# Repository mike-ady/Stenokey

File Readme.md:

# Stenokey

Stenographic keyboard

Stenokey is an open source do it yourself stenographic keyboard project.  It is aimed 
at makers with some electronics experience (soldering) and who own a 3D printer 
or who have a friend with a 3D printer.

Stenokey connects to any desktop or laptop PC that has a USB port.  It is meant 
to work with the Open Steno Project's Plover software, which runs on Linux, Mac and 
Windows.

This project consists of four main parts:

- The OpenSCAD source code for all of the 3D printed plastic parts is in the main 
directory.  Printer ready .STL files for the key tops are in the Key\_Print\_Files 
directory.  The .STL files for the case are in the Case\_Print\_Files directory.  

- The bill of materials (BOM) for populating the circuit board is in the main 
directory.  The PCB design files are in the PCB directory.

- The Arduino based firmware is in the Firmware directory.

- Documentation for the project, including build instructions, programming and testing 
instructions and a user manual are all in the Documentation Directory.

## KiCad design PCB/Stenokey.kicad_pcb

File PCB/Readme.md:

# Stenokey PCB Readme

Copyright © 2017, Mike Ady  
This file is part of the open source Stenokey project.  
This file is licensed under the Creative Commons Attribution-ShareAlike license.

## Directory Listing

- Gerbers -- This directory holds the files that are required to have circuit boards made.

- Stenokey.pretty -- This directory is the footprint library for the Stenokey project.

- Stenokey.kicad_pcb -- This is the circuit board layout file.

- Stenokey.kicad_wks -- This is the title block and frame layout file.

- Stenokey.lib -- This is the schematic library for the Stenokey project.

- Stenokey.pro -- This is the KiCAD project file.

- StenoKey.sch -- This is the schematic file.

- StenoKeyLogo.kicad_wks -- This is the Stenokey logo in KiCAD format.

The remaining files and directories were program generated.

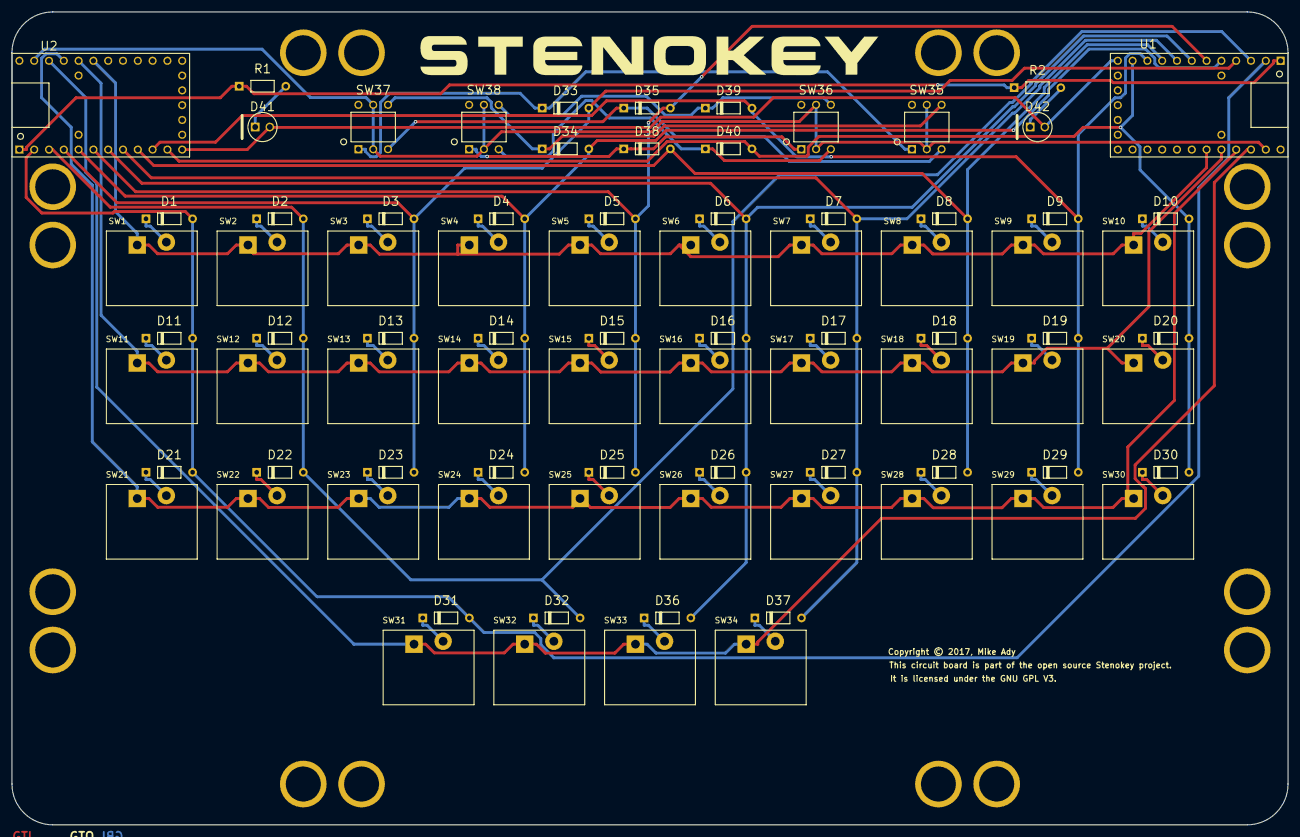
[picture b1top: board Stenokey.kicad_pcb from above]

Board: 2 copper layers, 219.0 x 139.5 mm, 102 parts (0 on the bottom side), 59 nets.

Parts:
D1, D2, D3, D4, D5, D6, D7, D8, D9, D10, D11, D12, D13, D14, D15, D16, D17, D18, D19, D20, D21, D22, D23, D24, D25, D26, D27, D28, D29, D30, D31, D32, D33, D34, D35, D36, D37, D38, D39, D40: DIODE; D4x2
D41, D42: LED; LED5X2.5
R1, R2: R; R4x2
SW1: KEY_R1C1; SW_Matias_Quiet
SW2: KEY_R1C2; SW_Matias_Quiet
SW3: KEY_R1C3; SW_Matias_Quiet
SW4: KEY_R1C4; SW_Matias_Quiet
SW5: KEY_R1C5; SW_Matias_Quiet
SW6: KEY_R1C6; SW_Matias_Quiet
SW7: KEY_R1C7; SW_Matias_Quiet
SW8: KEY_R1C8; SW_Matias_Quiet
SW9: KEY_R1C9; SW_Matias_Quiet
SW10: KEY_R1C10; SW_Matias_Quiet
SW11: KEY_R2C1; SW_Matias_Quiet
SW12: KEY_R2C2; SW_Matias_Quiet
SW13: KEY_R2C3; SW_Matias_Quiet
SW14: KEY_R2C4; SW_Matias_Quiet
SW15: KEY_R2C5; SW_Matias_Quiet
SW16: KEY_R2C6; SW_Matias_Quiet
SW17: KEY_R2C7; SW_Matias_Quiet
SW18: KEY_R2C8; SW_Matias_Quiet
SW19: KEY_R2C9; SW_Matias_Quiet
SW20: KEY_R2C10; SW_Matias_Quiet
SW21: KEY_R3C1; SW_Matias_Quiet
SW22: KEY_R3C2; SW_Matias_Quiet
SW23: KEY_R3C3; SW_Matias_Quiet
SW24: KEY_R3C4; SW_Matias_Quiet
SW25: KEY_R3C5; SW_Matias_Quiet
SW26: KEY_R3C6; SW_Matias_Quiet
SW27: KEY_R3C7; SW_Matias_Quiet
SW28: KEY_R3C8; SW_Matias_Quiet
SW29: KEY_R3C9; SW_Matias_Quiet
SW30: KEY_R3C10; SW_Matias_Quiet
SW31: KEY_R4C1; SW_Matias_Quiet
SW32: KEY_R4C2; SW_Matias_Quiet
SW33: KEY_R4C6; SW_Matias_Quiet
SW34: KEY_R4C7; SW_Matias_Quiet
SW35, SW36, SW37, SW38: SW_ENCODED; DIP6
U1, U2: Teensy2.0
Z1, Z2, Z3, Z4, Z5, Z6, Z7, Z8, Z9, Z10, Z11, Z12, Z13, Z14, Z15, Z16: Hole; HOLE_600800
Z17: Copyright
Z18: Logo; StenoKeyLogo

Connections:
/COL0: D1.2, D11.2, D21.2, D31.2, U1.2, U2.2
/COL1: D2.2, D12.2, D22.2, D32.2, U1.3, U2.3
/COL2: D3.2, D13.2, D23.2, D33.2, U1.4, U2.4
/COL3: D4.2, D14.2, D24.2, D34.2, U1.5, U2.5
/COL4: D5.2, D15.2, D25.2, D35.2, U1.6, U2.6
/COL5: D6.2, D16.2, D26.2, D36.2, U1.7, U2.7
/COL6: D7.2, D17.2, D27.2, D37.2, U1.8, U2.8
/COL7: D8.2, D18.2, D28.2, D38.2, U1.9, U2.9
/COL8: D9.2, D19.2, D29.2, D39.2, U1.10, U2.10
/COL9: D10.2, D20.2, D30.2, D40.2, U1.11, U2.11
/GND: R1.1, R2.1, U1.1, U2.1
/LED: D41.2, D42.2, U1.12, U2.12
/ROW0: SW1.1, SW2.1, SW3.1, SW4.1, SW5.1, SW6.1, SW7.1, SW8.1, SW9.1, SW10.1, U1.24, U2.24
/ROW1: SW11.1, SW12.1, SW13.1, SW14.1, SW15.1, SW16.1, SW17.1, SW18.1, SW19.1, SW20.1, U1.25, U2.25
/ROW2: SW21.1, SW22.1, SW23.1, SW24.1, SW25.1, SW26.1, SW27.1, SW28.1, SW29.1, SW30.1, U1.26, U2.26
/ROW3: SW31.1, SW32.1, SW33.1, SW34.1, U1.27, U2.27
/ROW4: SW35.2, SW35.5, SW36.2, SW36.5, SW37.2, SW37.5, SW38.2, SW38.5, U1.28, U2.28
unnamed: D1.1, SW1.2
unnamed: D2.1, SW2.2
unnamed: D3.1, SW3.2
unnamed: D4.1, SW4.2
unnamed: D5.1, SW5.2
unnamed: D6.1, SW6.2
unnamed: D7.1, SW7.2
unnamed: D8.1, SW8.2
unnamed: D9.1, SW9.2
unnamed: D10.1, SW10.2
unnamed: D11.1, SW11.2
unnamed: D12.1, SW12.2
unnamed: D13.1, SW13.2
unnamed: D14.1, SW14.2
unnamed: D15.1, SW15.2
unnamed: D16.1, SW16.2
unnamed: D17.1, SW17.2
unnamed: D18.1, SW18.2
unnamed: D19.1, SW19.2
unnamed: D20.1, SW20.2
unnamed: D21.1, SW21.2
unnamed: D22.1, SW22.2
unnamed: D23.1, SW23.2
unnamed: D24.1, SW24.2
unnamed: D25.1, SW25.2
unnamed: D26.1, SW26.2
unnamed: D27.1, SW27.2
unnamed: D28.1, SW28.2
unnamed: D29.1, SW29.2
unnamed: D30.1, SW30.2
unnamed: D31.1, SW31.2
unnamed: D32.1, SW32.2
unnamed: D33.1, SW35.1, SW37.1
unnamed: D34.1, SW35.4, SW37.4
unnamed: D35.1, SW35.3, SW37.3
unnamed: D36.1, SW33.2
unnamed: D37.1, SW34.2
unnamed: D38.1, SW36.1, SW38.1
unnamed: D39.1, SW36.4, SW38.4
unnamed: D40.1, SW36.3, SW38.3
unnamed: D41.1, R1.2
unnamed: D42.1, R2.2

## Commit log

2017-11-08 Initial commit.
2017-11-08 Added Readme.md and Licenst.txt files
2017-11-27 Update user manual. Update prototype photograph. Update key print files readme.
2020-02-25 Made minor changes to formatting and spelling and incidental changes to some text. Adjusted Dimension "InsertD2" in StenokeyCalse.scad to reduce possible upswelling around insert.
2020-02-25 Updated Readme.md with an actual photo of Stenokey with the clamshell case.

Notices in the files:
PCB/Stenokey.kicad_pcb:
The Stenokey circuit board is open source.  It is licensed under the GNU GPL V3.0.
parts and their libraries:
It is licensed under the GNU GPL V3.
